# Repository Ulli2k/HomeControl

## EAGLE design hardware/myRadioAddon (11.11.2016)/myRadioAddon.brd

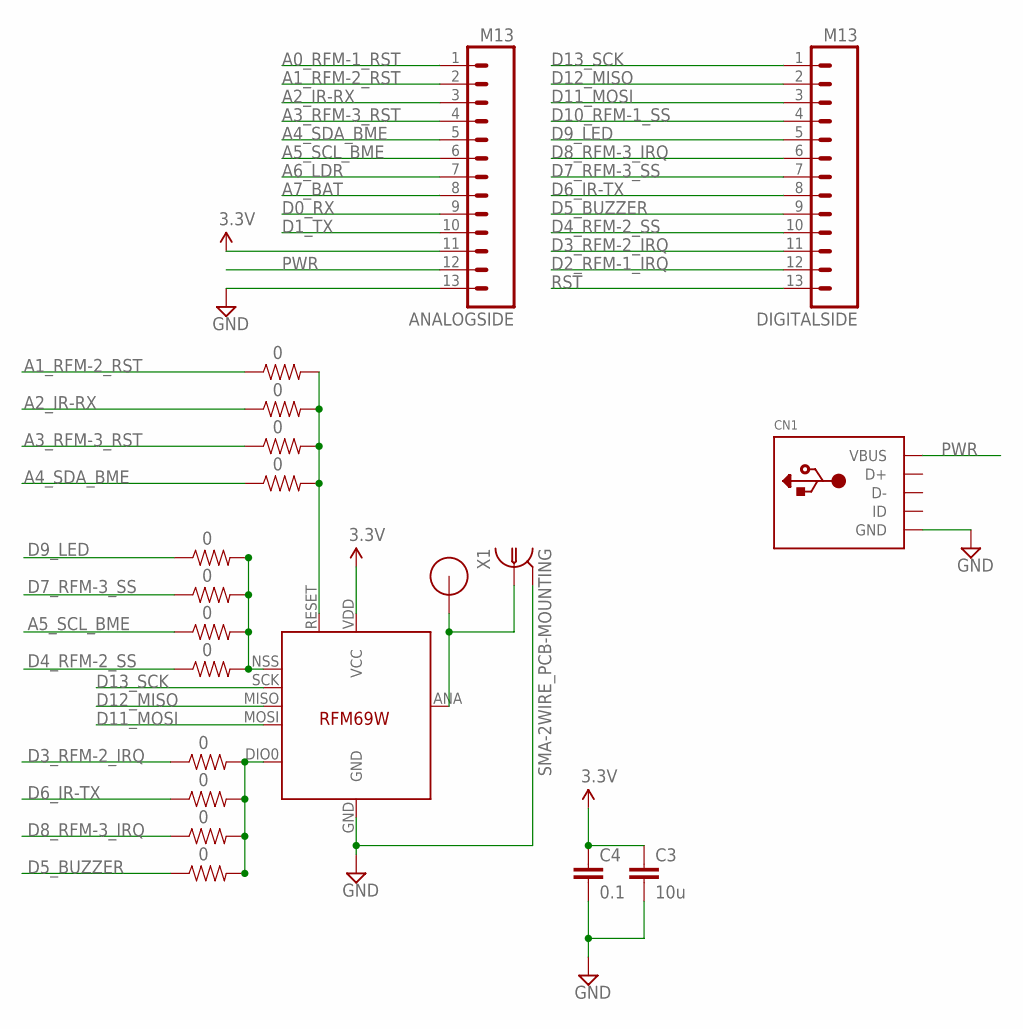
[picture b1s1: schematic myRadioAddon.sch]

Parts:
ANALOGSIDE: M13; 1X13
C3: 10u; 0805-CAP
C4: 0.1; 0603-CAP
CN1: USBMINIB; USB-MINIB
DIGITALSIDE: M13; 1X13
R1, R2, R3, R4, R5, R6, R7, R8, R9, R10, R11, R12: 0; 0603-RES
U$1: RFM12B_ANTENNA; RFM12B-ANTENNA
U$5: RFM69_MINIPADS; RFM69W-MINPADS
X1: SMA-2WIRE_PCB-MOUNTING; J01151A0931

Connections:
A0_RFM-1_RST: ANALOGSIDE.1
A1_RFM-2_RST: ANALOGSIDE.2, R3.1
A2_IR-RX: ANALOGSIDE.3, R7.1
A3_RFM-3_RST: ANALOGSIDE.4, R4.1
A4_SDA_BME: ANALOGSIDE.5, R10.1
A5_SCL_BME: ANALOGSIDE.6, R11.1
A6_LDR: ANALOGSIDE.7
A7_BAT: ANALOGSIDE.8
D0_RX: ANALOGSIDE.9
D1_TX: ANALOGSIDE.10
D2_RFM-1_IRQ: DIGITALSIDE.12
D3_RFM-2_IRQ: DIGITALSIDE.11, R1.1
D4_RFM-2_SS: DIGITALSIDE.10, R2.1
D5_BUZZER: DIGITALSIDE.9, R9.1
D6_IR-TX: DIGITALSIDE.8, R12.1
D7_RFM-3_SS: DIGITALSIDE.7, R6.1
D8_RFM-3_IRQ: DIGITALSIDE.6, R5.1
D9_LED: DIGITALSIDE.5, R8.1
D10_RFM-1_SS: DIGITALSIDE.4
D11_MOSI: DIGITALSIDE.3, U$5.MOSI
D12_MISO: DIGITALSIDE.2, U$5.MISO
D13_SCK: DIGITALSIDE.1, U$5.SCK
GND: ANALOGSIDE.13, C3.2, C4.2, CN1.GND, U$5.GND, X1.G@1 (2), X1.G@2 (2), X1.G@3 (2), X1.G@4 (2)
unnamed: R1.2, R5.2, R9.2, R12.2, U$5.DIO0 (DIO0/IRQ)
unnamed: R2.2, R6.2, R8.2, R11.2, U$5.NSS (SEL)
unnamed: U$1.P$1, U$5.ANA (ANT), X1.1
unnamed: R3.2, R4.2, R7.2, R10.2, U$5.RESET
PWR: ANALOGSIDE.12, CN1.VBUS
RST: DIGITALSIDE.13
VCC: ANALOGSIDE.11, C3.1, C4.1, U$5.VDD (VCC)

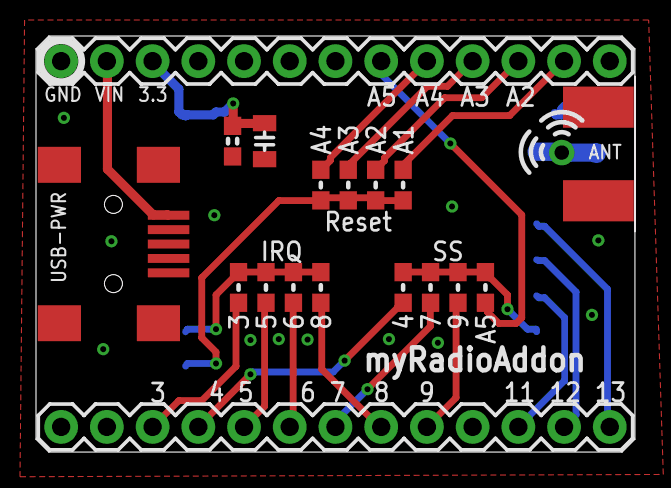
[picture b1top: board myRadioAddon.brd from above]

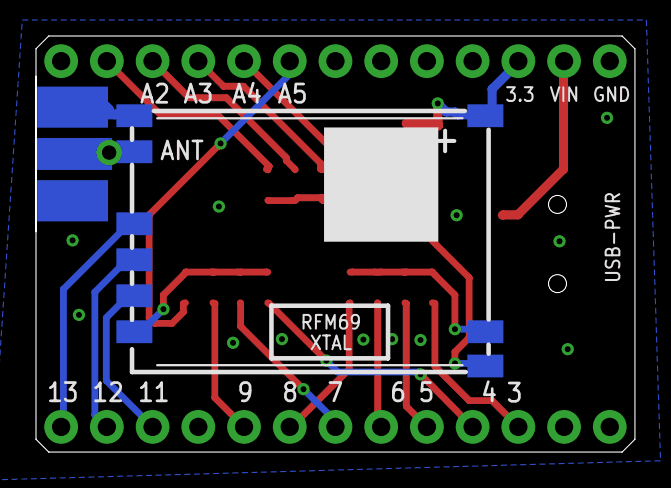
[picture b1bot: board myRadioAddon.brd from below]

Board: 2 copper layers, 33.3 x 23.1 mm, 20 parts (2 on the bottom side), 22 nets.

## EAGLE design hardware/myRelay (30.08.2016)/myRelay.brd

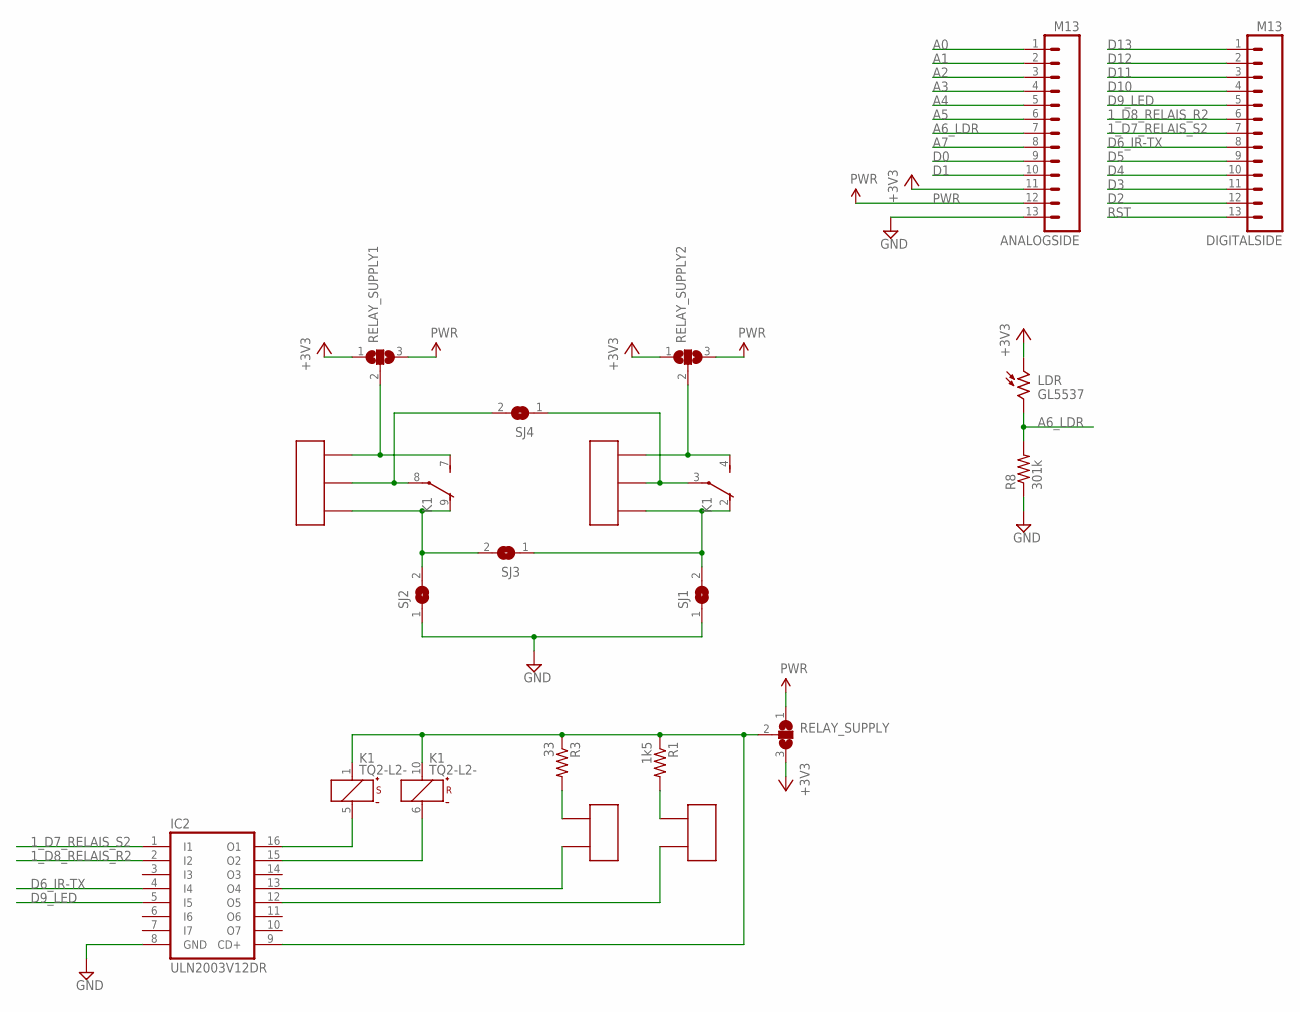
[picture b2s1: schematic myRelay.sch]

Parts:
ANALOGSIDE: M13; 1X13
DIGITALSIDE: M13; 1X13
IC2: ULN2003V12DR; SO16
K1: TQ2-L2-; TQ2; MPN TQ2-L2-3V
LDR: GL5537; M9960
R1: 1k5; 0603-RES
R3: 33; 0603-RES
R8: 301k; 0603-RES
RELAY_SUPPLY, RELAY_SUPPLY1, RELAY_SUPPLY2: SJ2WW; SJ_2W
SJ1, SJ2, SJ3, SJ4: SJW
U$1, U$2: HDR_3PINLUMBERG_KRMC; 1X03_LUMBERG-KRMC_3,5MM
U$3, U$4: HDR_2PIN; 1X02_NS

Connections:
1_D7_RELAIS_S2: DIGITALSIDE.7, IC2.1 (I1)
1_D8_RELAIS_R2: DIGITALSIDE.6, IC2.2 (I2)
+3V3: ANALOGSIDE.11, LDR.1, RELAY_SUPPLY.3, RELAY_SUPPLY1.1, RELAY_SUPPLY2.1
A0: ANALOGSIDE.1
A1: ANALOGSIDE.2
A2: ANALOGSIDE.3
A3: ANALOGSIDE.4
A4: ANALOGSIDE.5
A5: ANALOGSIDE.6
A6_LDR: ANALOGSIDE.7, LDR.2, R8.2
A7: ANALOGSIDE.8
D0: ANALOGSIDE.9
D1: ANALOGSIDE.10
D2: DIGITALSIDE.12
D3: DIGITALSIDE.11
D4: DIGITALSIDE.10
D5: DIGITALSIDE.9
D6_IR-TX: DIGITALSIDE.8, IC2.4 (I4)
D9_LED: DIGITALSIDE.5, IC2.5 (I5)
D10: DIGITALSIDE.4
D11: DIGITALSIDE.3
D12: DIGITALSIDE.2
D13: DIGITALSIDE.1
GND: ANALOGSIDE.13, IC2.8 (GND), R8.1, SJ1.1, SJ2.1
unnamed: K1.8, SJ4.2, U$1.2
unnamed: K1.9 (O), SJ2.2, SJ3.2, U$1.1
unnamed: K1.7 (S), RELAY_SUPPLY1.2, U$1.3
unnamed: R3.2, U$3.1
unnamed: IC2.16 (O1), K1.5 (-)
unnamed: IC2.15 (O2), K1.6 (-)
unnamed: IC2.13 (O4), U$3.2
unnamed: K1.4 (S), RELAY_SUPPLY2.2, U$2.1
unnamed: K1.2 (O), SJ1.2, SJ3.1, U$2.3
unnamed: R1.2, U$4.1
unnamed: K1.3, SJ4.1, U$2.2
unnamed: IC2.12 (O5), U$4.2
unnamed: IC2.9 (CD+), K1.1 (+), K1.10 (+), R1.1, R3.1, RELAY_SUPPLY.2
PWR: ANALOGSIDE.12, RELAY_SUPPLY.1, RELAY_SUPPLY1.3, RELAY_SUPPLY2.3
RST: DIGITALSIDE.13

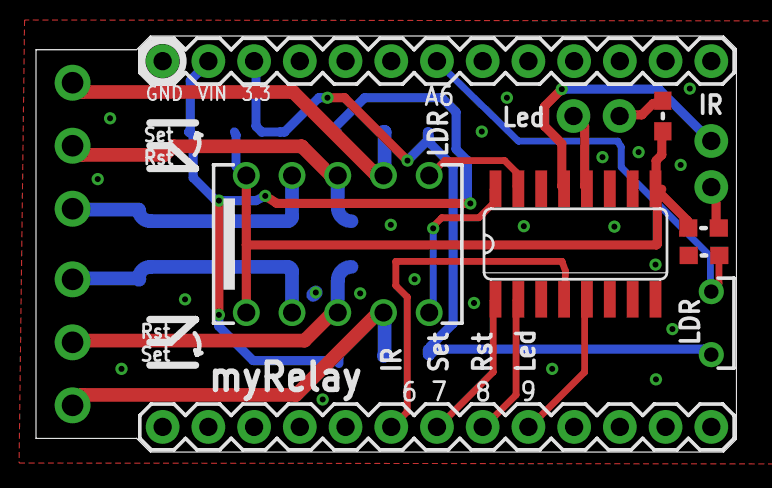
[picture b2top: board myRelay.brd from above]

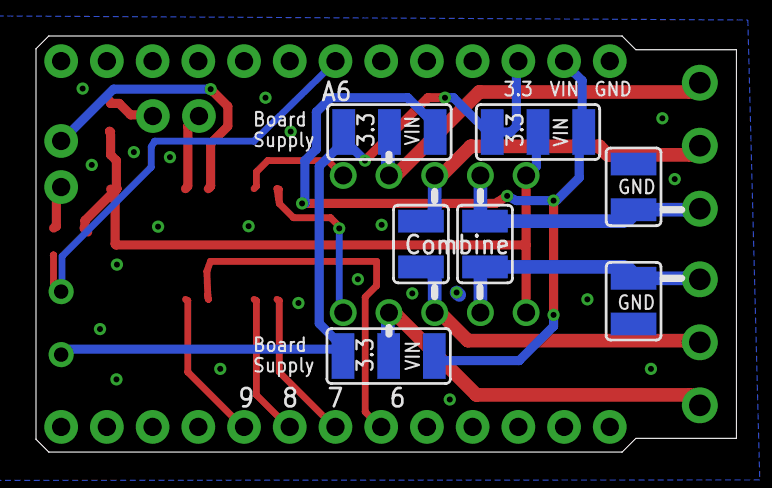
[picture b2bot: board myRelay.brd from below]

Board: 2 copper layers, 38.9 x 23.1 mm, 19 parts (7 on the bottom side), 21 nets.

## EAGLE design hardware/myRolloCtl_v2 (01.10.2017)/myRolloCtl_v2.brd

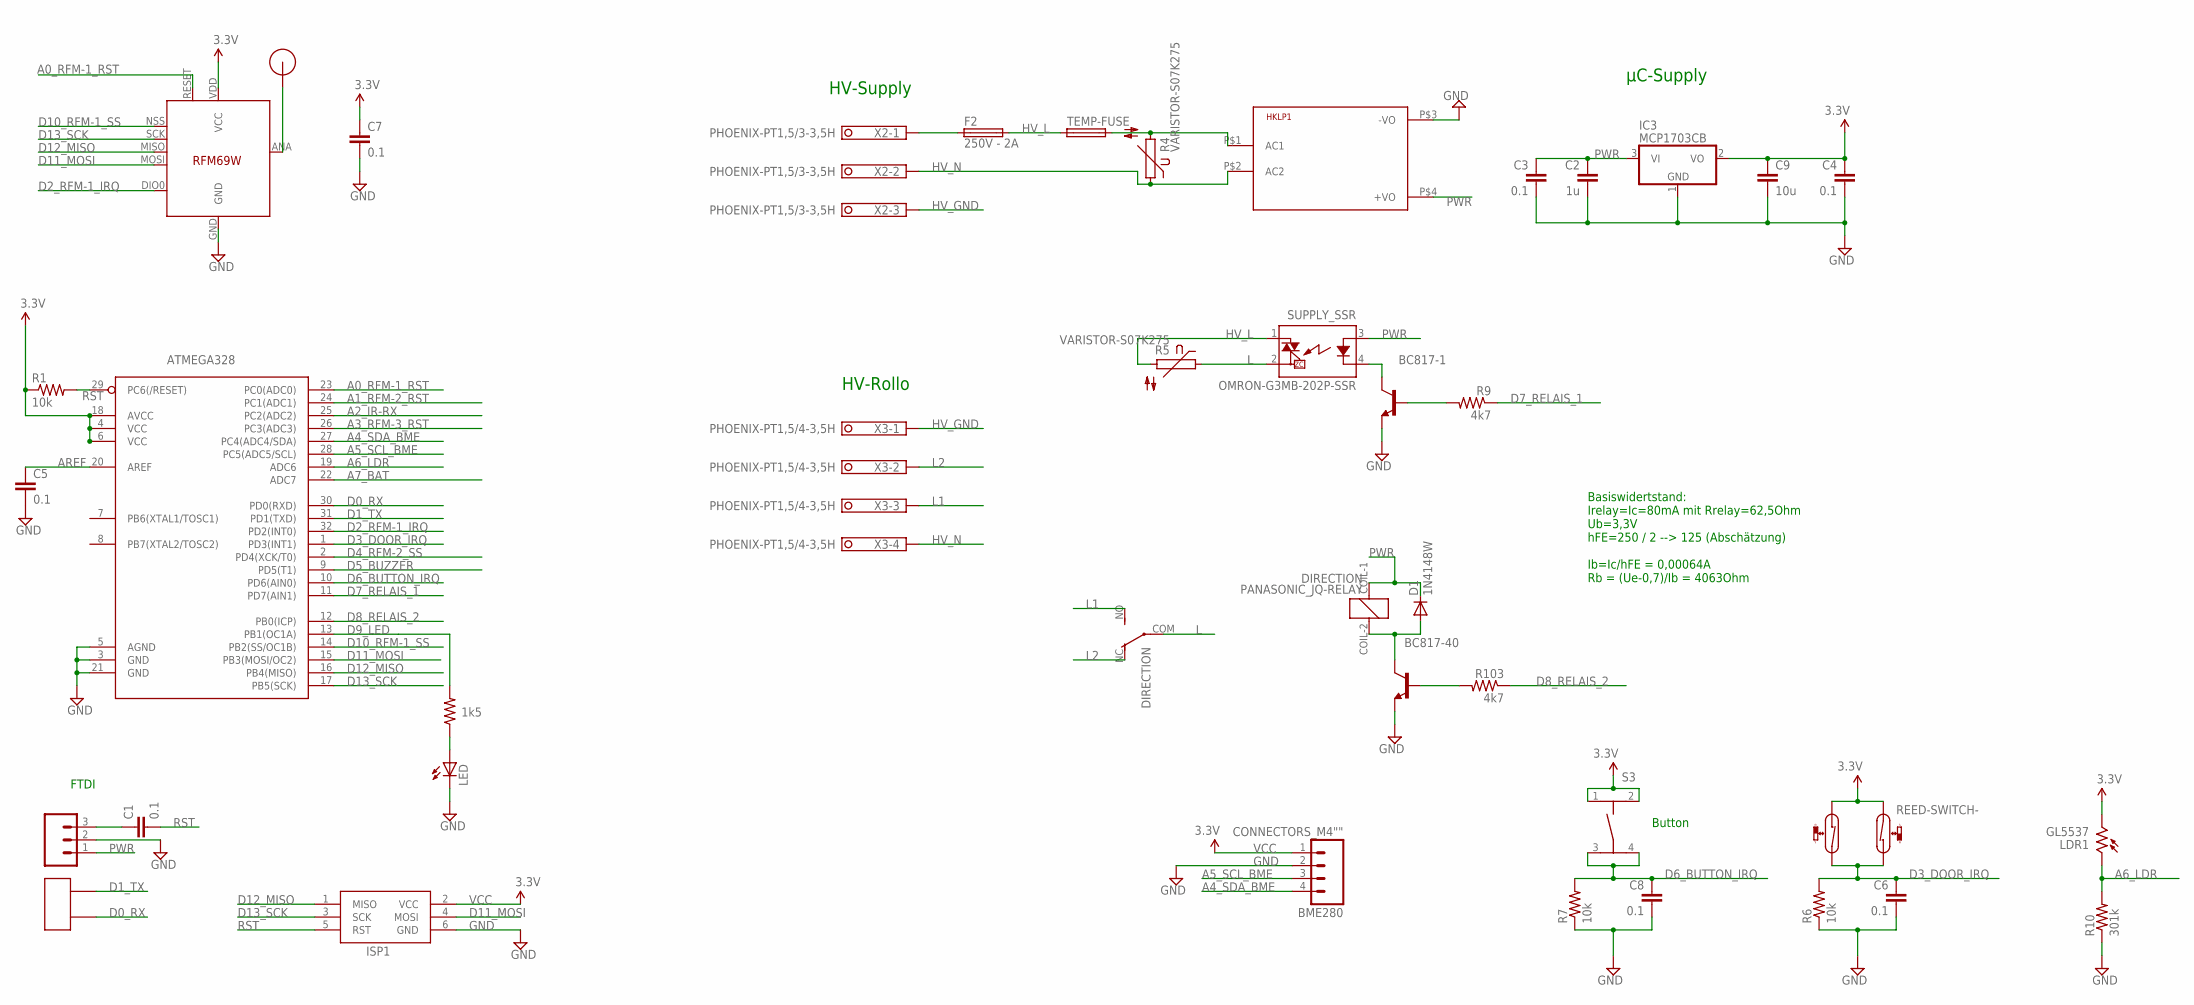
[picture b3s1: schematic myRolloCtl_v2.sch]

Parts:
ATMEGA328: ATMega-328; TQFP32-08
BC817-1, BC817-40: BC817-40-NPN-SOT23-BEC; SOT23-BEC
BME280: CONNECTORS_M4""; CONNECTORS_1X4
C1, C3, C4, C5, C6, C7, C8: 0.1; 0603-CAP
C2: 1u; 0603-CAP
C9: 10u; 0805-CAP
D1: 1N4148W; SOD123
DIRECTION: PANASONIC_JQ-RELAY; JQ1
F2: 250V - 2A; TE5
HKLP1: HKLPM01
IC3: MCP1703CB; SOT23
ISP1: AVRISP; AVRISP-EDGE
JP2: CONNECTORS_M3; CONNECTORS_1X3
LDR1: GL5537; M9960
LED: LED3MM
R1, R6, R7: 10k; 0603-RES
R2: 1k5; 0603-RES
R4, R5: VARISTOR-S07K275; S07K275
R9, R103: 4k7; 0603-RES
R10: 301k; 0603-RES
S1, S2: REED-SWITCH-; REED_15X2MM
S3: TASTER_SMD; TASTER-1254_SMD
SUPPLY_SSR: OMRON-G3MB-202P-SSR
TEMP-FUSE: FUSESW-102T; TEMP-FUSE
U$1: RFM12B_ANTENNA; RFM12B-ANTENNA
U$2: HDR_2PIN; 1X02_NS
U$5: RFM69_MINIPADS; RFM69W-MINPADS
X2: PHOENIX-PT1,5/3-3,5H; 1984620
X3: PHOENIX-PT1,5/4-3,5H; 1984633

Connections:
A0_RFM-1_RST: ATMEGA328.23 (PC0(ADC0)), U$5.RESET
A1_RFM-2_RST: ATMEGA328.24 (PC1(ADC1))
A2_IR-RX: ATMEGA328.25 (PC2(ADC2))
A3_RFM-3_RST: ATMEGA328.26 (PC3(ADC3))
A4_SDA_BME: ATMEGA328.27 (PC4(ADC4/SDA)), BME280.4
A5_SCL_BME: ATMEGA328.28 (PC5(ADC5/SCL)), BME280.3
A6_LDR: ATMEGA328.19 (ADC6), LDR1.1, R10.2
A7_BAT: ATMEGA328.22 (ADC7)
AREF: ATMEGA328.20 (AREF), C5.1
D0_RX: ATMEGA328.30 (PD0(RXD)), U$2.1
D1_TX: ATMEGA328.31 (PD1(TXD)), U$2.2
D2_RFM-1_IRQ: ATMEGA328.32 (PD2(INT0)), U$5.DIO0 (DIO0/IRQ)
D3_DOOR_IRQ: ATMEGA328.1 (PD3(INT1)), C6.1, R6.2, S1.2, S2.1
D4_RFM-2_SS: ATMEGA328.2 (PD4(XCK/T0))
D5_BUZZER: ATMEGA328.9 (PD5(T1))
D6_BUTTON_IRQ: ATMEGA328.10 (PD6(AIN0)), C8.1, R7.2, S3.3, S3.4
D7_RELAIS_1: ATMEGA328.11 (PD7(AIN1)), R9.1
D8_RELAIS_2: ATMEGA328.12 (PB0(ICP)), R103.1
D9_LED: ATMEGA328.13 (PB1(OC1A)), R2.2
D10_RFM-1_SS: ATMEGA328.14 (PB2(SS/OC1B)), U$5.NSS (SEL)
D11_MOSI: ATMEGA328.15 (PB3(MOSI/OC2)), ISP1.4 (MOSI), U$5.MOSI
D12_MISO: ATMEGA328.16 (PB4(MISO)), ISP1.1 (MISO), U$5.MISO
D13_SCK: ATMEGA328.17 (PB5(SCK)), ISP1.3 (SCK), U$5.SCK
GND: ATMEGA328.3 (GND), ATMEGA328.5 (AGND), ATMEGA328.21 (GND), BC817-1.E, BC817-40.E, BME280.2, C2.2, C3.2, C4.2, C5.2, C6.2, C7.2, C8.2, C9.2, HKLP1.P$3 (-VO), IC3.1 (GND), ISP1.6 (GND), JP2.2, LED.K (C), R6.1, R7.1, R10.1, U$5.GND
HV_GND: X2.3, X3.1
HV_L: F2.2, R5.2, SUPPLY_SSR.1 (DS1), TEMP-FUSE.1
HV_N: HKLP1.P$2 (AC2), R4.1, X2.2, X3.4
L: DIRECTION.COM, R5.1, SUPPLY_SSR.2 (DS2)
L1: DIRECTION.NO (S), X3.3
L2: DIRECTION.NC (O), X3.2
unnamed: BC817-1.B, R9.2
unnamed: LED.A, R2.1
unnamed: U$1.P$1, U$5.ANA (ANT)
unnamed: BC817-1.C, SUPPLY_SSR.4 (K)
unnamed: F2.1, X2.1
unnamed: HKLP1.P$1 (AC1), R4.2, TEMP-FUSE.2
unnamed: BC817-40.C, D1.A, DIRECTION.COIL-2 (2)
unnamed: C1.1, JP2.3
unnamed: BC817-40.B, R103.2
PWR: C2.1, C3.1, D1.C, DIRECTION.COIL-1 (1), HKLP1.P$4 (+VO), IC3.3 (VI), JP2.1, SUPPLY_SSR.3 (A)
RST: ATMEGA328.29 (PC6(/RESET)), C1.2, ISP1.5 (RST), R1.2
VCC: ATMEGA328.4 (VCC), ATMEGA328.6 (VCC), ATMEGA328.18 (AVCC), BME280.1, C4.1, C7.1, C9.1, IC3.2 (VO), ISP1.2 (VCC), LDR1.2, R1.1, S1.1, S2.2, S3.1, S3.2, U$5.VDD (VCC)

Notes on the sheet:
HV-Supply
HV-Rollo
µC-Supply
Basiswidertstand: Irelay=Ic=80mA mit Rrelay=62,5Ohm Ub=3,3V hFE=250 / 2 --> 125 (Abschätzung) Ib=Ic/hFE = 0,00064A Rb = (Ue-0,7)/Ib = 4063Ohm
Button
FTDI

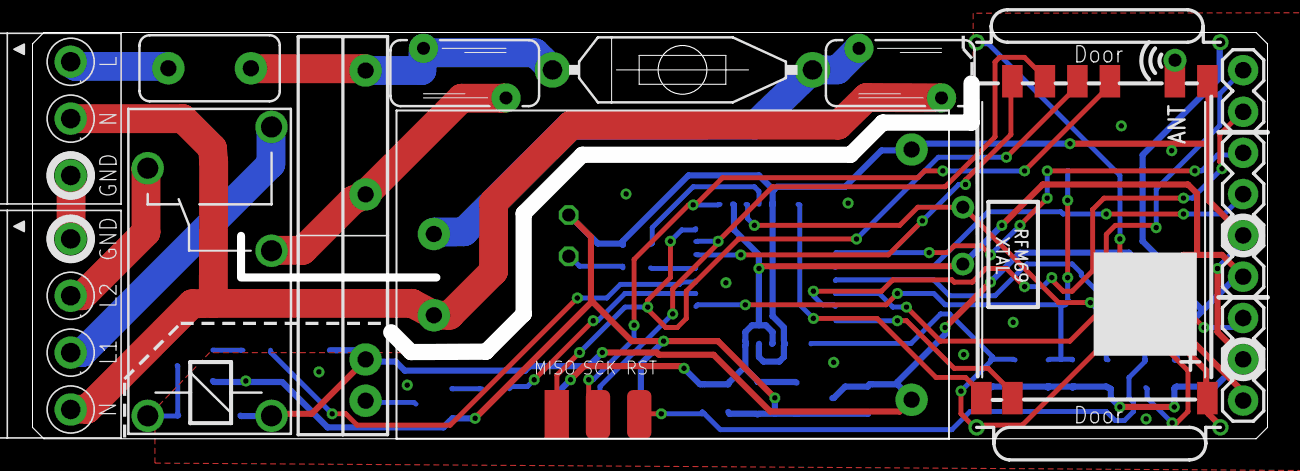
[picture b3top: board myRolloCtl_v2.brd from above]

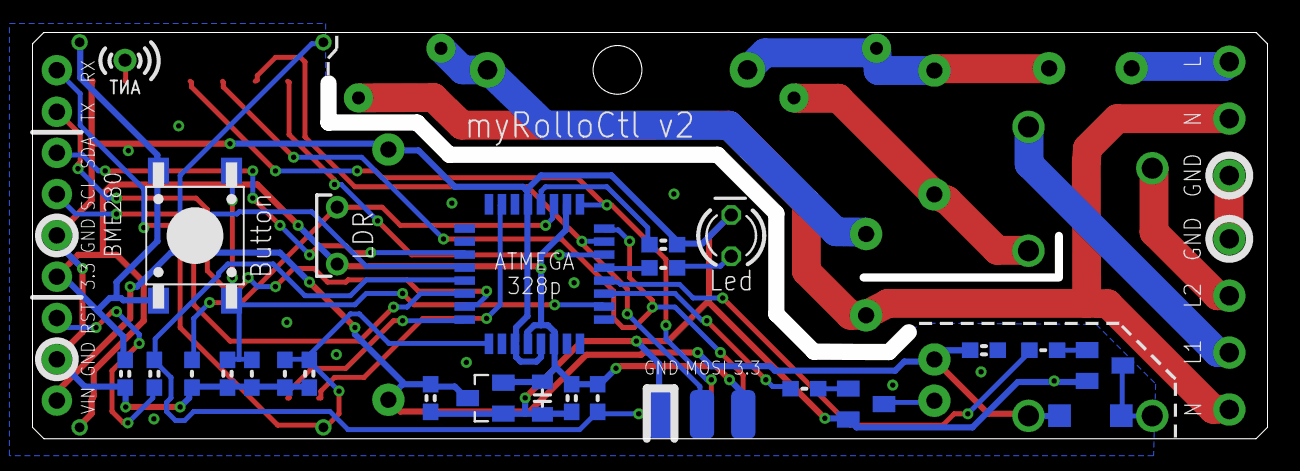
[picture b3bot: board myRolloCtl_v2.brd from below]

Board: 2 copper layers, 76.0 x 25.0 mm, 41 parts (25 on the bottom side), 36 nets.

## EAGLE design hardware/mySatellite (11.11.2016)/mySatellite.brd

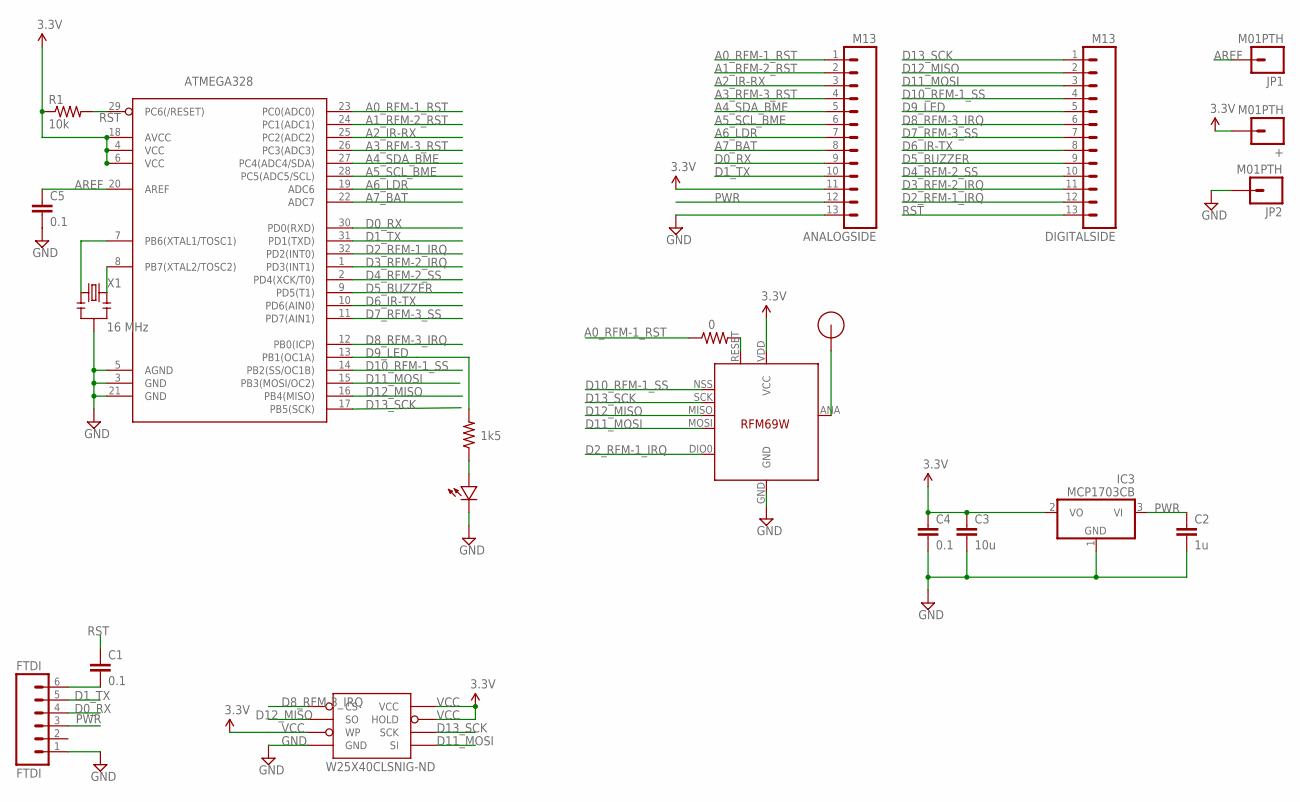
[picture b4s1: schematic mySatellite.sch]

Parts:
+: M01PTH; 1X01
ANALOGSIDE: M13; 1X13
ATMEGA328: ATMega-328; TQFP32-08
C1, C4, C5: 0.1; 0603-CAP
C2: 1u; 0603-CAP
C3: 10u; 0805-CAP
DIGITALSIDE: M13; 1X13
FTDI: FTDI; 1X06
IC3: MCP1703CB; SOT23
JP1, JP2: M01PTH; 1X01
R1: 10k; 0603-RES
R2: 1k5; 0603-RES
R3: 0; 0603-RES
U$1: RFM12B_ANTENNA; RFM12B-ANTENNA
U$2: LED0603; 0603-LED
U$5: RFM69_MINIPADS; RFM69W-MINPADS
W25X40CLSNIG-ND: AT25F512BWIDE_5.3MM; SO08WIDE
X1: 16 MHz; RESONATOR-SMD

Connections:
A0_RFM-1_RST: ANALOGSIDE.1, ATMEGA328.23 (PC0(ADC0)), R3.1
A1_RFM-2_RST: ANALOGSIDE.2, ATMEGA328.24 (PC1(ADC1))
A2_IR-RX: ANALOGSIDE.3, ATMEGA328.25 (PC2(ADC2))
A3_RFM-3_RST: ANALOGSIDE.4, ATMEGA328.26 (PC3(ADC3))
A4_SDA_BME: ANALOGSIDE.5, ATMEGA328.27 (PC4(ADC4/SDA))
A5_SCL_BME: ANALOGSIDE.6, ATMEGA328.28 (PC5(ADC5/SCL))
A6_LDR: ANALOGSIDE.7, ATMEGA328.19 (ADC6)
A7_BAT: ANALOGSIDE.8, ATMEGA328.22 (ADC7)
AREF: ATMEGA328.20 (AREF), C5.1, JP1.1
D0_RX: ANALOGSIDE.9, ATMEGA328.30 (PD0(RXD)), FTDI.4
D1_TX: ANALOGSIDE.10, ATMEGA328.31 (PD1(TXD)), FTDI.5
D2_RFM-1_IRQ: ATMEGA328.32 (PD2(INT0)), DIGITALSIDE.12, U$5.DIO0 (DIO0/IRQ)
D3_RFM-2_IRQ: ATMEGA328.1 (PD3(INT1)), DIGITALSIDE.11
D4_RFM-2_SS: ATMEGA328.2 (PD4(XCK/T0)), DIGITALSIDE.10
D5_BUZZER: ATMEGA328.9 (PD5(T1)), DIGITALSIDE.9
D6_IR-TX: ATMEGA328.10 (PD6(AIN0)), DIGITALSIDE.8
D7_RFM-3_SS: ATMEGA328.11 (PD7(AIN1)), DIGITALSIDE.7
D8_RFM-3_IRQ: ATMEGA328.12 (PB0(ICP)), DIGITALSIDE.6, W25X40CLSNIG-ND.1 (CS)
D9_LED: ATMEGA328.13 (PB1(OC1A)), DIGITALSIDE.5, R2.2
D10_RFM-1_SS: ATMEGA328.14 (PB2(SS/OC1B)), DIGITALSIDE.4, U$5.NSS (SEL)
D11_MOSI: ATMEGA328.15 (PB3(MOSI/OC2)), DIGITALSIDE.3, U$5.MOSI, W25X40CLSNIG-ND.5 (SI)
D12_MISO: ATMEGA328.16 (PB4(MISO)), DIGITALSIDE.2, U$5.MISO, W25X40CLSNIG-ND.2 (SO)
D13_SCK: ATMEGA328.17 (PB5(SCK)), DIGITALSIDE.1, U$5.SCK, W25X40CLSNIG-ND.6 (SCK)
GND: ANALOGSIDE.13, ATMEGA328.3 (GND), ATMEGA328.5 (AGND), ATMEGA328.21 (GND), C2.2, C3.2, C4.2, C5.2, FTDI.1, IC3.1 (GND), JP2.1, U$2.MINUS, U$5.GND, W25X40CLSNIG-ND.4 (GND), X1.2
unnamed: ATMEGA328.7 (PB6(XTAL1/TOSC1)), X1.1
unnamed: R2.1, U$2.PLUS
unnamed: U$1.P$1, U$5.ANA (ANT)
unnamed: R3.2, U$5.RESET
unnamed: C1.2, FTDI.6
unnamed: ATMEGA328.8 (PB7(XTAL2/TOSC2)), X1.3
PWR: ANALOGSIDE.12, C2.1, FTDI.3, IC3.3 (VI)
RST: ATMEGA328.29 (PC6(/RESET)), C1.1, DIGITALSIDE.13, R1.2
VCC: +.1, ANALOGSIDE.11, ATMEGA328.4 (VCC), ATMEGA328.6 (VCC), ATMEGA328.18 (AVCC), C3.1, C4.1, IC3.2 (VO), R1.1, U$5.VDD (VCC), W25X40CLSNIG-ND.3 (WP), W25X40CLSNIG-ND.7 (HOLD), W25X40CLSNIG-ND.8 (VCC)

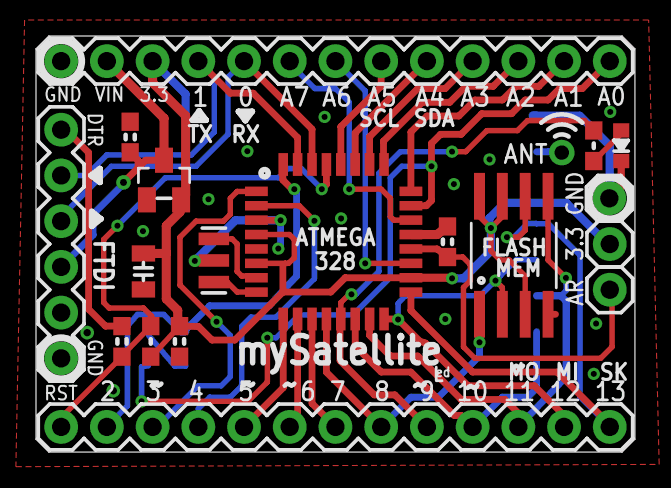
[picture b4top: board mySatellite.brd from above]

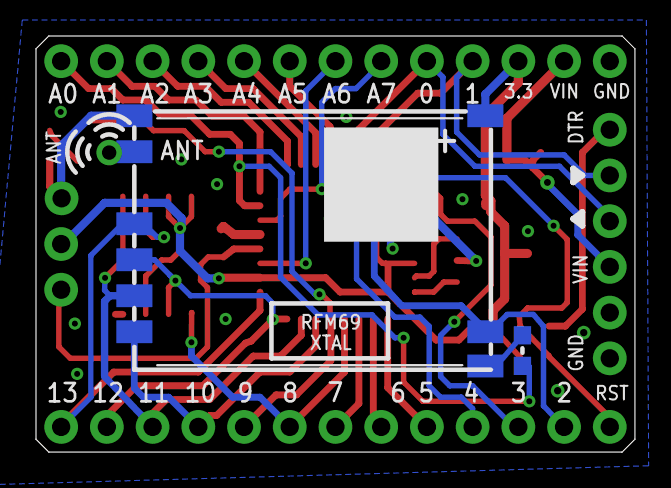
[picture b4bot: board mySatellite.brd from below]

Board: 2 copper layers, 33.3 x 23.1 mm, 21 parts (2 on the bottom side), 33 nets.

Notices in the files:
parts and their libraries:
SparkFun-Connectors: Licensing: CC v3.0 Share-Alike You are welcome to use this library for commercial purposes.
